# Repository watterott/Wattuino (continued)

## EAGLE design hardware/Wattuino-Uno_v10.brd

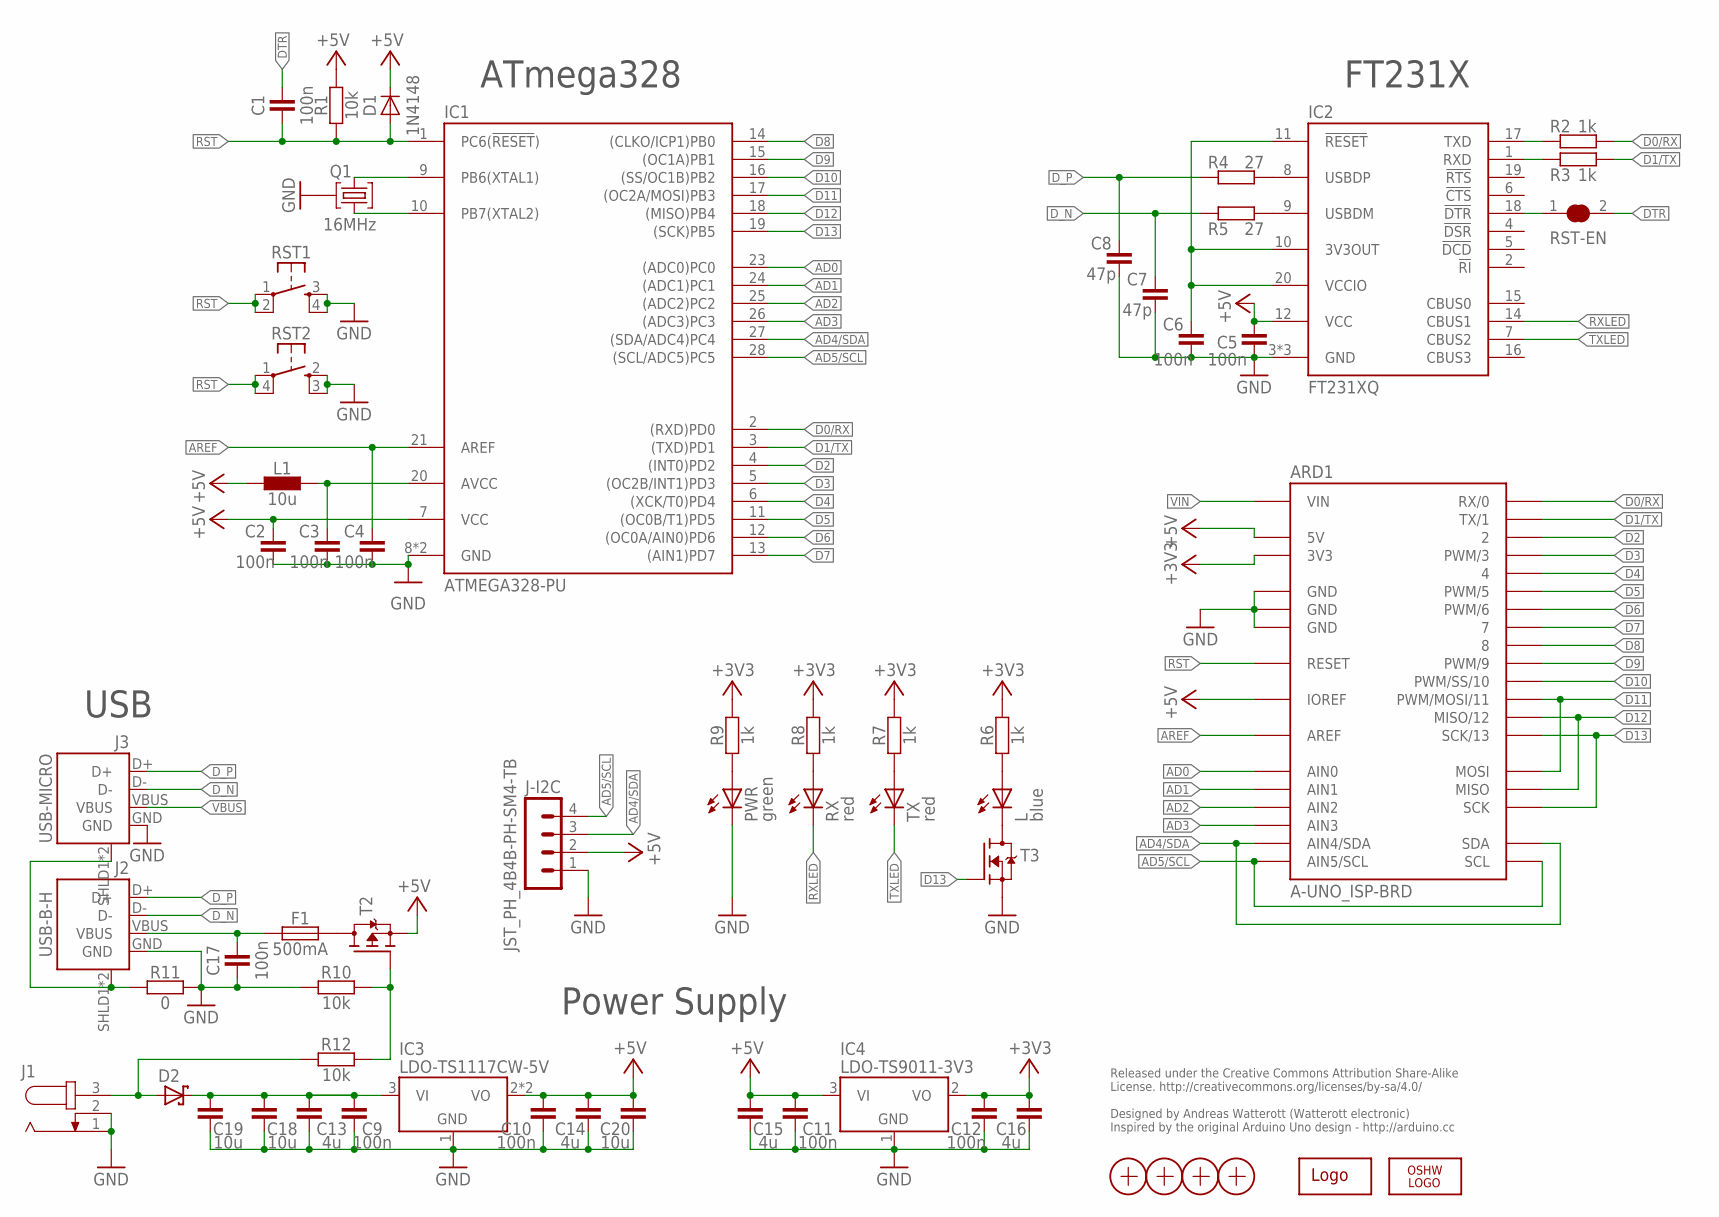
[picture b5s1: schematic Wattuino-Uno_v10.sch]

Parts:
ARD1: A-UNO_ISP-BRD; A-UNO-ISP
C1, C2, C3, C4, C5, C6, C9, C10, C11, C12, C17: 100n; C0402
C7, C8: 47p; C0402
C13, C14, C15, C16: 4u; C0603
C18, C19, C20: 10u; C1206
D1: 1N4148; SOD110
D2: D_SCHOTTKY-SS14; SMA_DO214AC
F1: 500mA; C0805
IC1: ATMEGA328-PU; DIL28
IC2: FT231XQ; QFN20-PAD
IC3: LDO-TS1117CW-5V; SOT223
IC4: LDO-TS9011-3V3; SOT23
J1: DC-JACK
J2: USB-B-H
J3: USB-MICRO; USB-MICRO-10103594
J-I2C: JST_PH_4B4B-PH-SM4-TB; JST_B4B-PH-SM4-TB
L: blue; C0603
L1: 10u; C0603
LOGO1: LOGO-S_PLACE_M; SPARK_TPLACE_M
LOGO2: OSHW_LOGOX0100; OSHW_6X100
PWR: green; C0603
Q1: 16MHz; CRYSTAL_32X13
R1, R10, R12: 10k; C0402
R2, R3, R6, R7, R8, R9: 1k; C0402
R4, R5: 27; C0402
R11: 0; C0402
RST1: SW-TACTILE-PTS840P; SW_PTS840P
RST2: SW-TACTILE-TL3315; SW_TL3315N
RST-EN: JUMPER2-0603
RX: red; C0603
T2: MOSFET-P-SOT23; SOT23
T3: MOSFET-N-SOT23; SOT23
TX: red; C0603
X1, X2, X3, X4: PASSER-07; PASSER_07MM

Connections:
3V3OUT: C6.2, IC2.10 (3V3OUT), IC2.11 (!RESET), IC2.20 (VCCIO)
+3V3: ARD1.3V3, C12.2, C16.2, IC4.2 (VO), R6.2, R7.2, R8.2, R9.2
+5V: ARD1.5V, ARD1.IOREF, ARD1.VCC (5V), C2.2, C5.2, C10.2, C11.2, C14.2, C15.2, C20.2, D1.C, IC1.7 (VCC), IC2.12 (VCC), IC3.2 (VO), IC3.4 (VO), IC4.3 (VI), J-I2C.2, L1.1, R1.2, T2.2 (S)
AD0: ARD1.A0 (AIN0), IC1.23 ((ADC0)PC0)
AD1: ARD1.A1 (AIN1), IC1.24 ((ADC1)PC1)
AD2: ARD1.A2 (AIN2), IC1.25 ((ADC2)PC2)
AD3: ARD1.A3 (AIN3), IC1.26 ((ADC3)PC3)
AD4/SDA: ARD1.A4 (AIN4/SDA), ARD1.SDA, IC1.27 ((SDA/ADC4)PC4), J-I2C.3
AD5/SCL: ARD1.A5 (AIN5/SCL), ARD1.SCL, IC1.28 ((SCL/ADC5)PC5), J-I2C.4
AREF: ARD1.AREF, C4.2, IC1.21 (AREF)
AVCC: C3.2, IC1.20 (AVCC), L1.2
D0/RX: ARD1.0 (RX/0), IC1.2 ((RXD)PD0), R2.2
D1/TX: ARD1.1 (TX/1), IC1.3 ((TXD)PD1), R3.2
D2: ARD1.2, IC1.4 ((INT0)PD2)
D3: ARD1.3 (PWM/3), IC1.5 ((OC2B/INT1)PD3)
D4: ARD1.4, IC1.6 ((XCK/T0)PD4)
D5: ARD1.5 (PWM/5), IC1.11 ((OC0B/T1)PD5)
D6: ARD1.6 (PWM/6), IC1.12 ((OC0A/AIN0)PD6)
D7: ARD1.7, IC1.13 ((AIN1)PD7)
D8: ARD1.8, IC1.14 ((CLKO/ICP1)PB0)
D9: ARD1.9 (PWM/9), IC1.15 ((OC1A)PB1)
D10: ARD1.10 (PWM/SS/10), IC1.16 ((SS/OC1B)PB2)
D11: ARD1.11 (PWM/MOSI/11), ARD1.MOSI, IC1.17 ((OC2A/MOSI)PB3)
D12: ARD1.12 (MISO/12), ARD1.MISO, IC1.18 ((MISO)PB4)
D13: ARD1.13 (SCK/13), ARD1.SCK, IC1.19 ((SCK)PB5), T3.1 (G)
DN: IC2.9 (USBDM), R5.2
DP: IC2.8 (USBDP), R4.2
DTR: C1.2, RST-EN.2
DTR_FT: IC2.18 (!DTR), RST-EN.1
D_N: C7.2, J2.D-, J3.D-, R5.1
D_P: C8.2, J2.D+, J3.D+, R4.1
GND: ARD1.GND@1 (GND), ARD1.GND@2 (GND), ARD1.GND@3 (GND), ARD1.GND@4 (GND), C2.1, C3.1, C4.1, C5.1, C6.1, C7.1, C8.1, C9.1, C10.1, C11.1, C12.1, C13.1, C14.1, C15.1, C16.1, C17.1, C18.1, C19.1, C20.1, IC1.8 (GND), IC1.22 (GND), IC2.3 (GND), IC2.13 (GND), IC2.TP (GND), IC3.1 (GND), IC4.1 (GND), J1.1, J1.2, J2.GND, J3.GND, J-I2C.1, PWR.C, Q1.GND, R10.1, R11.2, RST1.3 (S1), RST1.4 (S2), RST2.2 (S1), RST2.3 (S2), T3.2 (S)
unnamed: PWR.A, R9.1
unnamed: L.C, T3.3 (D)
unnamed: L.A, R6.1
unnamed: R7.1, TX.A
unnamed: R8.1, RX.A
RST: ARD1.RST (RESET), ARD1.RST2 (RESET), C1.1, D1.A, IC1.1 (PC6(!RESET!)), R1.1, RST1.1, RST1.2, RST2.1, RST2.4 (P2)
RXLED: IC2.14 (CBUS1), RX.C
RX_FT: IC2.1 (RXD), R3.1
SHLD: J2.SHLD1 (SHIELD), J2.SHLD2 (SHIELD), J3.SHLD1 (SHIELD), J3.SHLD2 (SHIELD), R11.1
TXLED: IC2.7 (CBUS2), TX.C
TX_FT: IC2.17 (TXD), R2.1
USBVCC: F1.2, T2.3 (D)
VBUS: C17.2, F1.1, J2.VBUS, J3.VBUS
VEXT: D2.A, J1.3, R12.1
VEXT2: R10.2, R12.2, T2.1 (G)
VIN: ARD1.VIN, C9.2, C13.2, C18.2, C19.2, D2.C, IC3.3 (VI)
XTAL1: IC1.9 (PB6(XTAL1)), Q1.2
XTAL2: IC1.10 (PB7(XTAL2)), Q1.1

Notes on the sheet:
Released under the Creative Commons Attribution Share-Alike License. http://creativecommons.org/licenses/by-sa/4.0/ Designed by Andreas Watterott (Watterott electronic) Inspired by the original Arduino Uno design - http://arduino.cc
ATmega328
FT231X
USB
Power Supply

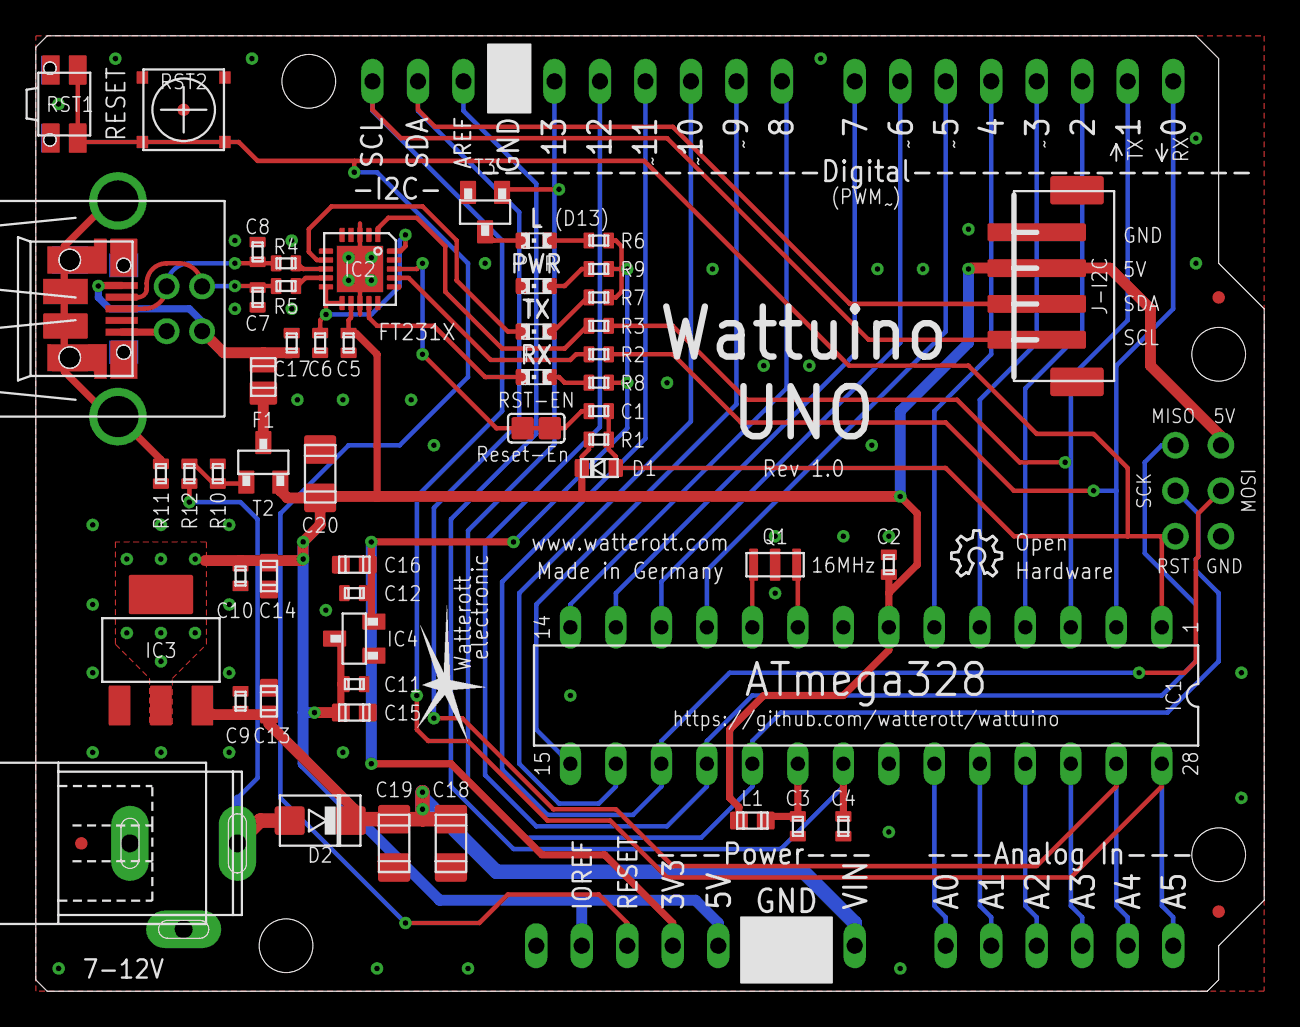
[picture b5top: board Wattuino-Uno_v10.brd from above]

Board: 2 copper layers, 68.6 x 53.3 mm, 61 parts (0 on the bottom side), 50 nets.

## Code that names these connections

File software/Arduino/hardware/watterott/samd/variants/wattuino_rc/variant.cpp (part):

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 |            |                  |        |                 |   EIC  | ADC |  AC | PTC | DAC | SERCOMx | SERCOMx |  TCCx  |  TCCx  |    COM   | AC/GLCK  |
 |            |                  |        |                 |(EXTINT)|(AIN)|(AIN)|     |     | (x/PAD) | (x/PAD) | (x/WO) | (x/WO) |          |          |
 +------------+------------------+--------+-----------------+--------+-----+-----+-----+-----+---------+---------+--------+--------+----------+----------+
 | 00         | D0               |  PA22  |                 |  *06   |     |     | X10 |     |   3/00  |   5/00  |* TC4/0 | TCC0/4 |          | GCLK_IO6 |
 | 01         | D1               |  PA23  |                 |  *07   |     |     | X11 |     |   3/01  |   5/01  |* TC4/1 | TCC0/5 | USB/SOF  | GCLK_IO7 |
 | 02         | D2               |  PA10  |                 |   10   | *18 |     | X02 |     |   0/02  |   2/02  |*TCC1/0 | TCC0/2 | I2S/SCK0 | GCLK_IO4 |
 | 03         | D3               |  PA11  |                 |   11   | *19 |     | X03 |     |   0/03  |   2/03  |*TCC1/1 | TCC0/3 | I2S/FS0  | GCLK_IO5 |
 | 04         | D4               |  PB10  |                 |  *10   |     |     |     |     |         |   4/02  |* TC5/0 | TCC0/4 | I2S/MCK1 | GCLK_IO4 |
 | 05         | D5               |  PB11  |                 |  *11   |     |     |     |     |         |   4/03  |* TC5/1 | TCC0/5 | I2S/SCK1 | GCLK_IO5 |
 | 06         | D6               |  PA20  |                 |  *04   |     |     | X08 |     |   5/02  |   3/02  |        |*TCC0/6 | I2S/SCK0 | GCLK_IO4 |
 | 07         | D7               |  PA21  |                 |  *05   |     |     | X09 |     |   5/03  |   3/03  |        |*TCC0/7 | I2S/FS0  | GCLK_IO5 |
 +------------+------------------+--------+-----------------+--------+-----+-----+-----+-----+---------+---------+--------+--------+----------+----------+
 */
  { PORTA, 22, PIO_DIGITAL, (PIN_ATTR_DIGITAL|PIN_ATTR_PWM|PIN_ATTR_TIMER    ), No_ADC_Channel, PWM4_CH0,   TC4_CH0,      EXTERNAL_INT_6    },
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 |            |                  |        |                 |(EXTINT)|(AIN)|(AIN)|     |     | (x/PAD) | (x/PAD) | (x/WO) | (x/WO) |          |          |
 +------------+------------------+--------+-----------------+--------+-----+-----+-----+-----+---------+---------+--------+--------+----------+----------+
 |            |       SPI        |        |                 |        |     |     |     |     |         |         |        |        |          |          |
 | 08         | MOSI             |  PA16  |                 |  *00   |     |     | X04 |     |  *1/00  |   3/00  |*TCC2/0 | TCC0/6 |          | GCLK_IO2 |
 | 09         | SCK              |  PA17  |                 |  *01   |     |     | X05 |     |  *1/01  |   3/01  | TCC2/1 | TCC0/7 |          | GCLK_IO3 |
 | 10         | MISO             |  PA19  |                 |   03   |     |     | X07 |     |  *1/03  |   3/03  |* TC3/1 | TCC0/3 | I2S/SD0  | AC/CMP1  |
 +------------+------------------+--------+-----------------+--------------------+-----+-----+---------+---------+--------+--------+----------+----------+
 |            |       Wire       |        |                 |        |     |     |     |     |         |         |        |        |          |          |
 | 11         | SDA              |  PA08  |                 |   NMI  | *16 |     | X00 |     |  *0/00  |   2/00  | TCC0/0 | TCC1/2 | I2S/SD1  |          |
 | 12         | SCL              |  PA09  |                 |   09   | *17 |     | X01 |     |  *0/01  |   2/01  | TCC0/1 | TCC1/3 | I2S/MCK0 |          |
 +------------+------------------+--------+-----------------+--------+-----+-----+-----+-----+---------+---------+--------+--------+----------+----------+
 |            |      Serial1     |        |                 |        |     |     |     |     |         |         |        |        |          |          |
 | 13         | RX               |  PB23  |                 |   07   |     |     |     |     |         |  *5/03  |        |        |          | GCLK_IO1 |
 | 14         | TX               |  PB22  |                 |   06   |     |     |     |     |         |  *5/02  |        |        |          | GCLK_IO0 |
 +------------+------------------+--------+-----------------+--------+-----+-----+-----+-----+---------+---------+--------+--------+----------+----------+
 */
                                                                                                                                               // DIPO=3 DOPO=0
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 |            |                  |        |                 |   EIC  | ADC |  AC | PTC | DAC | SERCOMx | SERCOMx |  TCCx  |  TCCx  |    COM   | AC/GLCK  |
 |            |                  |        |                 |(EXTINT)|(AIN)|(AIN)|     |     | (x/PAD) | (x/PAD) | (x/WO) | (x/WO) |          |          |
 +------------+------------------+--------+-----------------+--------+-----+-----+-----+-----+---------+---------+--------+--------+----------+----------+
 | 15         | A0 / DAC0        |  PA02  |                 |   02   | *00 |     | Y00 | OUT |         |         |        |        |          |          |
 | 16         | A1               |  PB02  |                 |  *02   | *10 |     | Y08 |     |         |   5/00  |        |        |          |          |
 | 17         | A2               |  PB03  |                 |  *03   | *11 |     | Y09 |     |         |   5/01  |        |        |          |          |
 | 18         | A3               |  PA04  |                 |   04   | *04 |  00 | Y02 |     |         |   0/00  |*TCC0/0 |        |          |          |
 | 19         | A4               |  PA05  |                 |   05   | *05 |  01 | Y03 |     |         |   0/01  |*TCC0/1 |        |          |          |
 | 20         | A5               |  PA06  |                 |   06   | *06 |  02 | Y04 |     |         |   0/02  | TCC1/0 |        |          |          |
 | 21         | A6               |  PA07  |                 |   07   | *07 |  03 | Y05 |     |         |   0/03  | TCC1/1 |        | I2S/SD0  |          |
 +------------+------------------+--------+-----------------+--------+-----+-----+-----+-----+---------+---------+--------+--------+----------+----------+
 */
  { PORTA,  2, PIO_ANALOG,  (PIN_ATTR_DIGITAL|PIN_ATTR_ANALOG /*DAC*/        ), ADC_Channel0,   NOT_ON_PWM, NOT_ON_TIMER, EXTERNAL_INT_NONE },
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 |            |                  |        |                 |(EXTINT)|(AIN)|(AIN)|     |     | (x/PAD) | (x/PAD) | (x/WO) | (x/WO) |          |          |
 +------------+------------------+--------+-----------------+--------+-----+-----+-----+-----+---------+---------+--------+--------+----------+----------+
 |            |       USB        |        |                 |        |     |     |     |     |         |         |        |        |          |          |
 | 22         |                  |  PA24  | USB N           |   12   |     |     |     |     |   3/02  |   5/02  |  TC5/0 | TCC1/2 | USB/DM   |          |
 | 23         |                  |  PA25  | USB P           |   13   |     |     |     |     |   3/03  |   5/03  |  TC5/1 | TCC1/3 | USB/DP   |          |
 | 24         |                  |  PA18  | USB ID          |   02   |     |     | X06 |     |   1/02  |   3/02  |  TC3/0 | TCC0/2 |          | AC/CMP0  |
 +------------+------------------+--------+-----------------+--------+-----+-----+-----+-----+---------+---------+--------+--------+----------+----------+
 | 25         | A7/AREF          |  PA03  |                 |   03   |  01 |     | Y01 |     |         |         |        |        |          |          |
 +------------+------------------+--------+-----------------+--------+-----+-----+-----+-----+---------+---------+--------+--------+----------+----------+
 */
  { PORTA, 24, PIO_COM,     (PIN_ATTR_NONE                                   ), No_ADC_Channel, NOT_ON_PWM, NOT_ON_TIMER, EXTERNAL_INT_NONE }, // USB/DM
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 | 33         |                  |  PB09  | WINC IRQN       |  *09   |  03 |     | Y15 |     |         |   4/01  |  TC4/1 |        |          |          |
 +------------+------------------+--------+-----------------+--------+-----+-----+-----+-----+---------+---------+--------+--------+----------+----------+
 |            | 32768Hz Crystal  |        |                 |        |     |     |     |     |         |         |        |        |          |          |
 | 34         |                  |  PA00  | XIN32           |   00   |     |     |     |     |         |   1/00  | TCC2/0 |        |          |          |
 | 35         |                  |  PA01  | XOUT32          |   01   |     |     |     |     |         |   1/01  | TCC2/1 |        |          |          |
 +------------+------------------+--------+-----------------+--------+-----+-----+-----+-----+---------+---------+--------+--------+----------+----------+
 | 36         | SWD PINS         |  PA30  | SWCLK           |        |     |     |     |     |         |         |        |        |          |          |
 | 37         |                  |  PA31  | SWDIO           |        |     |     |     |     |         |         |        |        |          |          |
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
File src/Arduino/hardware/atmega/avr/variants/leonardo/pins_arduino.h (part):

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
// ATMEL ATMEGA32U4 / ARDUINO LEONARDO
//
// D0				PD2					RXD1/INT2
// D1				PD3					TXD1/INT3
// D2				PD1		SDA			SDA/INT1
// D3#				PD0		PWM8/SCL	OC0B/SCL/INT0
// D4		A6		PD4					ADC8
// D5#				PC6		???			OC3A/#OC4A
// D6#		A7		PD7		FastPWM		#OC4D/ADC10
// D7				PE6					INT6/AIN0
//
// D8		A8		PB4					ADC11/PCINT4
// D9#		A9		PB5		PWM16		OC1A/#OC4B/ADC12/PCINT5
// D10#		A10		PB6		PWM16		OC1B/0c4B/ADC13/PCINT6
// D11#				PB7		PWM8/16		0C0A/OC1C/#RTS/PCINT7
// D12		A11		PD6					T1/#OC4D/ADC9
// D13#				PC7		PWM10		CLK0/OC4A
//
// A0		D18		PF7					ADC7
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//
// New pins D14..D17 to map SPI port to digital pins
//
// MISO		D14		PB3					MISO,PCINT3
// SCK		D15		PB1					SCK,PCINT1
// MOSI		D16		PB2					MOSI,PCINT2
// SS		D17		PB0					RXLED,SS/PCINT0
//
// TXLED			PD5
// RXLED		    PB0
// HWB				PE2					HWB

// these arrays map port names (e.g. port B) to the
// appropriate addresses for various functions (e.g. reading
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};

const uint8_t PROGMEM digital_pin_to_port_PGM[] = {
	PD, // D0 - PD2
	PD,	// D1 - PD3
	PD, // D2 - PD1
	PD,	// D3 - PD0
	PD,	// D4 - PD4
	PC, // D5 - PC6
	PD, // D6 - PD7
	PE, // D7 - PE6
	
	PB, // D8 - PB4
	PB,	// D9 - PB5
	PB, // D10 - PB6
	PB,	// D11 - PB7
	PD, // D12 - PD6
	PC, // D13 - PC7
	
	PB,	// D14 - MISO - PB3
	PB,	// D15 - SCK - PB1
	PB,	// D16 - MOSI - PB2
	PB,	// D17 - SS - PB0
	
	PF,	// D18 - A0 - PF7
	PF, // D19 - A1 - PF6
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	PF, // D22 - A4 - PF1
	PF, // D23 - A5 - PF0
	
	PD, // D24 / D4 - A6 - PD4
	PD, // D25 / D6 - A7 - PD7
	PB, // D26 / D8 - A8 - PB4
	PB, // D27 / D9 - A9 - PB5
	PB, // D28 / D10 - A10 - PB6
	PD, // D29 / D12 - A11 - PD6
};

const uint8_t PROGMEM digital_pin_to_bit_mask_PGM[] = {
	_BV(2), // D0 - PD2
	_BV(3),	// D1 - PD3
	_BV(1), // D2 - PD1
	_BV(0),	// D3 - PD0
	_BV(4),	// D4 - PD4
	_BV(6), // D5 - PC6
	_BV(7), // D6 - PD7
	_BV(6), // D7 - PE6
	
	_BV(4), // D8 - PB4
	_BV(5),	// D9 - PB5
	_BV(6), // D10 - PB6
	_BV(7),	// D11 - PB7
	_BV(6), // D12 - PD6
	_BV(7), // D13 - PC7
	
	_BV(3),	// D14 - MISO - PB3
	_BV(1),	// D15 - SCK - PB1
	_BV(2),	// D16 - MOSI - PB2
	_BV(0),	// D17 - SS - PB0
	
	_BV(7),	// D18 - A0 - PF7
	_BV(6), // D19 - A1 - PF6
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	_BV(1), // D22 - A4 - PF1
	_BV(0), // D23 - A5 - PF0
	
	_BV(4), // D24 / D4 - A6 - PD4
	_BV(7), // D25 / D6 - A7 - PD7
	_BV(4), // D26 / D8 - A8 - PB4
	_BV(5), // D27 / D9 - A9 - PB5
	_BV(6), // D28 / D10 - A10 - PB6
	_BV(6), // D29 / D12 - A11 - PD6
};

const uint8_t PROGMEM digital_pin_to_timer_PGM[] = {
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	4,	// A3				PF4					ADC4
	1,	// A4				PF1					ADC1	
	0,	// A5				PF0					ADC0	
	8,	// A6		D4		PD4					ADC8
	10,	// A7		D6		PD7					ADC10
	11,	// A8		D8		PB4					ADC11
	12,	// A9		D9		PB5					ADC12
	13,	// A10		D10		PB6					ADC13
	9	// A11		D12		PD6					ADC9
};

#endif /* ARDUINO_MAIN */
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
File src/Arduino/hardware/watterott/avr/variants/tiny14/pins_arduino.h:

/*
  pins_arduino.c - pin definitions for the Arduino board
  Part of Arduino / Wiring Lite

  Copyright (c) 2005 David A. Mellis

  This library is free software; you can redistribute it and/or
  modify it under the terms of the GNU Lesser General Public
  License as published by the Free Software Foundation; either
  version 2.1 of the License, or (at your option) any later version.

  This library is distributed in the hope that it will be useful,
  but WITHOUT ANY WARRANTY; without even the implied warranty of
  MERCHANTABILITY or FITNESS FOR A PARTICULAR PURPOSE.  See the GNU
  Lesser General Public License for more details.

  You should have received a copy of the GNU Lesser General
  Public License along with this library; if not, write to the
  Free Software Foundation, Inc., 59 Temple Place, Suite 330,
  Boston, MA  02111-1307  USA

  $Id: pins_arduino.c 565 2009-03-25 10:50:00Z dmellis $

  Modified 28-08-2009 for attiny84 R.Wiersma
  Modified 09-10-2009 for attiny45 A.Saporetti
  Modified 29-05-2015 for attiny841 A.Watterott
*/

#ifndef Pins_Arduino_h
#define Pins_Arduino_h

#include <avr/pgmspace.h>

// ATMEL ATTINY84 / ARDUINO
//
//                           +-\/-+
//                     VCC  1|    |14  GND
//             (D 10)  PB0  2|    |13  PA0  (D  0)        AREF
//             (D  9)  PB1  3|    |12  PA1  (D  1) 
//                     PB3  4|    |11  PA2  (D  2) 
//  PWM  INT0  (D  8)  PB2  5|    |10  PA3  (D  3) 
//  PWM        (D  7)  PA7  6|    |9   PA4  (D  4) 
//  PWM        (D  6)  PA6  7|    |8   PA5  (D  5)        PWM
//                           +----+

static const uint8_t A0 = 0;
static const uint8_t A1 = 1;
static const uint8_t A2 = 2;
static const uint8_t A3 = 3;
static const uint8_t A4 = 4;
static const uint8_t A5 = 5;
static const uint8_t A6 = 6;
static const uint8_t A7 = 7;

#if defined(__AVR_ATtinyX41__) || defined(__AVR_ATtiny441__) || defined(__AVR_ATtiny841__)
static const uint8_t A8 = 8;
static const uint8_t A9 = 9;
static const uint8_t A10 = 10;
static const uint8_t A11 = 11;

static const uint8_t SS   = 7;
static const uint8_t MOSI = 6;
static const uint8_t MISO = 5;
static const uint8_t SCK  = 4;

static const uint8_t SDA = 6;
static const uint8_t SCL = 4;

#define LED_BUILTIN 8
#endif

#define digitalPinToPCICR(p)    ( ((p) >= 0 && (p) <= 10) ? (&GIMSK) : ((uint8_t *)0) )
#define digitalPinToPCICRbit(p) ( ((p) <= 7) ? PCIE0 : PCIE1 )
#define digitalPinToPCMSK(p)    ( ((p) <= 7) ? (&PCMSK0) : (((p) <= 10) ? (&PCMSK1) : ((uint8_t *)0)) )
#define digitalPinToPCMSKbit(p) ( ((p) <= 7) ? (p) : (10 - (p)) )

#ifdef ARDUINO_MAIN

// these arrays map port names (e.g. port B) to the
// appropriate addresses for various functions (e.g. reading
// and writing)
const uint16_t PROGMEM port_to_mode_PGM[] = 
{
  NOT_A_PORT,
  (uint16_t)&DDRA,
  (uint16_t)&DDRB,
};

const uint16_t PROGMEM port_to_output_PGM[] = 
{
  NOT_A_PORT,
  (uint16_t)&PORTA,
  (uint16_t)&PORTB,
};

const uint16_t PROGMEM port_to_input_PGM[] = 
{
  NOT_A_PORT,
  (uint16_t)&PINA,
  (uint16_t)&PINB,
};

const uint8_t PROGMEM digital_pin_to_port_PGM[] = 
{
  PA, /* 0 */
  PA,
  PA,
  PA,
  PA,
  PA,
  PA,
  PA,
  PB, /* 8 */
  PB,
  PB,
};

const uint8_t PROGMEM digital_pin_to_bit_mask_PGM[] = 
{
  _BV(0), /* port A */
  _BV(1),
  _BV(2),
  _BV(3),
  _BV(4),
  _BV(5), 
  _BV(6),
  _BV(7),
  _BV(2), /* port B */
  _BV(1),
  _BV(0),
};

#if defined(__AVR_ATtinyX41__) || defined(__AVR_ATtiny441__) || defined(__AVR_ATtiny841__)
const uint8_t PROGMEM digital_pin_to_timer_PGM[] = 
{
  NOT_ON_TIMER,
  NOT_ON_TIMER, /* TOCC0 */
  NOT_ON_TIMER, /* TOCC1 */
  NOT_ON_TIMER, /* TOCC2 */
  NOT_ON_TIMER, /* TOCC3 */
  NOT_ON_TIMER, /* TOCC4 */
  NOT_ON_TIMER, /* TOCC5 */
  NOT_ON_TIMER, /* TOCC6 */
  NOT_ON_TIMER, /* TOCC7 */
  NOT_ON_TIMER,
  NOT_ON_TIMER,
};

#else
const uint8_t PROGMEM digital_pin_to_timer_PGM[] = 
{
  NOT_ON_TIMER,
  NOT_ON_TIMER,
  NOT_ON_TIMER,
  NOT_ON_TIMER, 
  NOT_ON_TIMER,
  TIMER1B, /* OC1B */
  TIMER1A, /* OC1A */
  TIMER0B, /* OC0B */
  TIMER0A, /* OC0A */
  NOT_ON_TIMER,
  NOT_ON_TIMER,
};
#endif

#endif

#endif

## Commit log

2012-04-04 update readme add layout files
2012-04-04 add license information
2012-04-07 add Optiboot bootloader
2012-04-07 code clean-up update to Optiboot 4.5
2012-04-07 change to new UART defines
2012-05-11 update image
2012-08-07 updated image
2012-08-30 added Eagle symbol (thanks to Jens Bachmann)
2012-12-10 changed drill size to 0.9mm
2013-01-25 added Fritzing part
2013-01-25 updated Fritzing part
2013-04-23 updated to Optiboot v5.0 (March 2013)
2014-03-10 updated license infos
2014-03-10 added optiboot with lower watchdog time
2015-01-01 renamed files
2015-01-01 moved files
2015-01-01 added Arduino bootloader and extensions
2015-01-03 updated Micronucleus infos
2015-01-11 updated board group name
2015-01-11 moved image
2015-01-27 added caterina bootloader with custom VID+PID
2015-01-27 added support for caterina with custom VID+PID
2015-01-27 updaetd readme
2015-01-27 added caterina.inf
2015-01-28 added Tiny85 layout and schematics
2015-02-01 updated USB vid+pid
2015-02-03 updated Tiny85/Nanite85
2015-02-17 added ZIP archive
2015-02-18 changed file names to lower case
2015-03-13 updated board support package
2015-04-14 updated BSP
2015-05-06 updated layout and schematics
2015-05-06 updated/added images
2015-05-08 added Wattuino Uno
2015-05-26 updated schematics
2015-06-01 updated Micronucleus
2015-06-01 added Tiny841/Nanite841
2015-06-01 added tiny841 support
2015-06-04 updated ZIP archive
2015-06-13 updated images
2015-06-22 updated bootloader
2015-06-24 added Board Manager URL
2015-07-27 updated docu
2015-07-27 updated bootloaders
2015-08-17 updated info
2015-08-21 changed path structure
2015-08-21 updated checksum
2015-08-21 updated links
2015-09-22 updated bsp links
2015-09-25 updated BSP file names
2015-10-23 updated docu and readme
2016-02-20 added ATmega328PB optiboot
2016-02-21 updated infos
2016-02-23 added Wattuino Pro Mini PB
2016-02-23 added blink example
2016-03-04 added OptiLoader
2016-04-26 updated fuse settings
2016-05-02 added new micronucleus binary for osx, which works with nanite841
2016-05-03 added standard pins
2016-05-03 updated boards
2016-05-03 updated upload tool
2016-05-03 updated fuses
2016-05-08 moved erase and locking
2016-06-09 added Nanite841 rev 1.1
2016-06-09 added Nanite85 rev 1.1
2016-06-19 Added udev rule note to readme
2016-06-20 updated pathes
2016-07-21 removed lock bit programming
2016-07-21 updated m32u4/leonardo variant
2016-07-21 updated micronucleus tool
2016-07-23 updated tiny cores
2016-07-26 updated avrdude.conf
2016-07-27 updated parameters for IDE 1.6.10
2016-07-27 updated programmers
2016-07-28 updated variant pin defines
2016-07-28 removed versions info from avr-gcc and avrdude
2016-08-01 removed avr-gcc and avrdude from toolsDependencies
2016-08-01 updated lock bits
2016-08-06 fake efuse for mega8
2016-08-08 removed compiler parameters
2016-08-08 removed programmers
2016-08-08 added info for mega8 fake efuse
2016-08-08 added ISP pins
2016-08-09 added avrdude parameters
2016-08-09 updated AVRdude parameters
2016-08-09 Revert "updated upload tool"
    This reverts commit bd2fe4794665e52c313962d48d5db69555fac078.
2016-08-20 added compiler parameters
2016-08-21 added avrdude 6.3 in "toolsDependencies"
2016-08-21 updated link
2016-08-27 cleaned up makefile
2016-09-02 cleaned up code
2016-09-02 removed custom core
2016-09-03 updated FTDI drivers to v2.12.18
2016-09-24 updated tools dependencies
2016-09-24 removed avrdude 6.3 dependencies
2016-09-24 removed tools dependencies (not needed vor Arduino v1.6.12+)
2016-10-04 added Pro Mini ISP connection
2016-10-05 moved infos to readme
2016-10-08 updated makefile
2016-11-01 new micronucleus binary for osx
2016-11-27 clean-up
2016-12-01 updated pins
2017-04-09 added samd boards
2017-05-04 updated examples
2017-05-23 BSP moved to github.com/watterott/Arduino-Boards
2017-06-07 added Wattuino RC v1.0
2018-09-21 added SAM-BAR
